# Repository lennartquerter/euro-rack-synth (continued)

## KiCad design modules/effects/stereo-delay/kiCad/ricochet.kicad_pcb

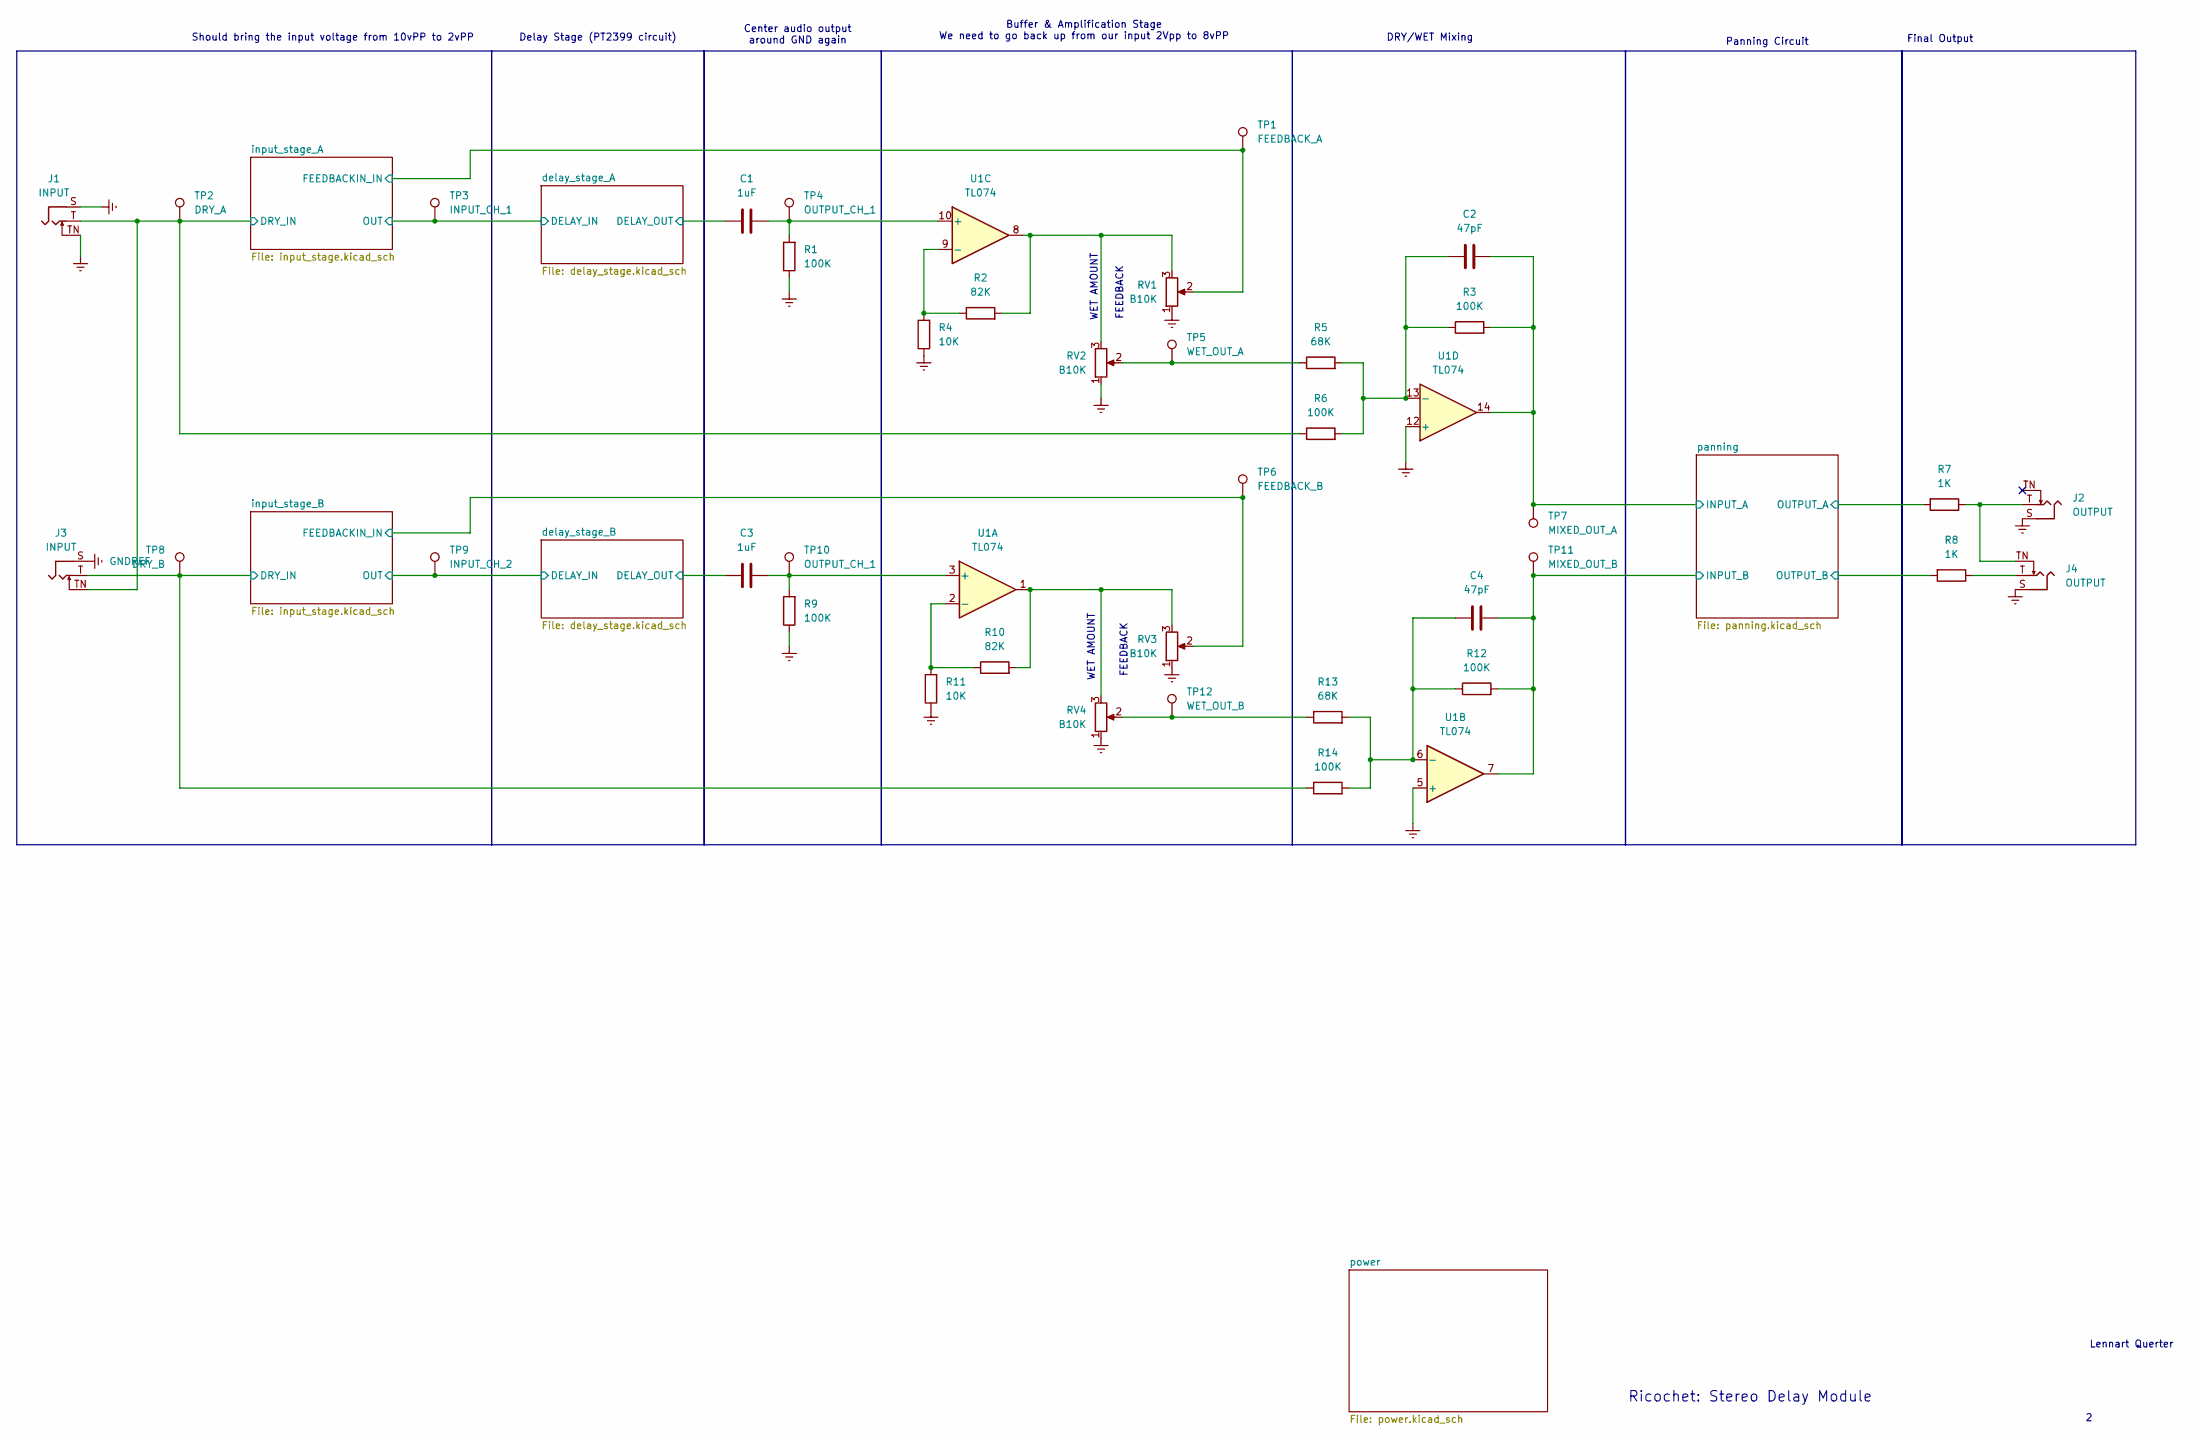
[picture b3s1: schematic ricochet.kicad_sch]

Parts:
C1, C3: 1uF; C_0805_2012Metric_Pad1.18x1.45mm_HandSolder
C2, C4: 47pF; C_0805_2012Metric_Pad1.18x1.45mm_HandSolder
J1, J3: INPUT; Jack_3.5mm_QingPu_WQP-PJ398SM_Vertical_CircularHoles
J2, J4: OUTPUT; Jack_3.5mm_QingPu_WQP-PJ398SM_Vertical_CircularHoles
R1, R3, R6, R9, R12, R14: 100K; R_0805_2012Metric_Pad1.20x1.40mm_HandSolder
R2, R10: 82K; R_0805_2012Metric_Pad1.20x1.40mm_HandSolder
R4, R11: 10K; R_0805_2012Metric_Pad1.20x1.40mm_HandSolder
R5, R13: 68K; R_0805_2012Metric_Pad1.20x1.40mm_HandSolder
R7, R8: 1K; R_0805_2012Metric_Pad1.20x1.40mm_HandSolder
RV1, RV2, RV3, RV4: B10K; Potentiometer_TT_P0915N
TP1: FEEDBACK_A; Pin_D1.0mm_L10.0mm
TP2: DRY_A; Pin_D1.0mm_L10.0mm
TP3: INPUT_CH_1; Pin_D1.0mm_L10.0mm
TP4, TP10: OUTPUT_CH_1; Pin_D1.0mm_L10.0mm
TP5: WET_OUT_A; Pin_D1.0mm_L10.0mm
TP6: FEEDBACK_B; Pin_D1.0mm_L10.0mm
TP7: MIXED_OUT_A; Pin_D1.0mm_L10.0mm
TP8: DRY_B; Pin_D1.0mm_L10.0mm
TP9: INPUT_CH_2; Pin_D1.0mm_L10.0mm
TP11: MIXED_OUT_B; Pin_D1.0mm_L10.0mm
TP12: WET_OUT_B; Pin_D1.0mm_L10.0mm
U1: TL074; SOIC-14

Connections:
/delay_stage_A/DELAY_IN: TP3.1; also elsewhere on the board
/delay_stage_A/DELAY_OUT: C1.1; also elsewhere on the board
/delay_stage_B/DELAY_IN: TP9.1; also elsewhere on the board
/delay_stage_B/DELAY_OUT: C3.1; also elsewhere on the board
/input_stage_A/DRY_IN: J1.T, J3.TN, R6.1, TP2.1; also elsewhere on the board
/input_stage_A/FEEDBACKIN_IN: RV1.2, TP1.1; also elsewhere on the board
/input_stage_B/DRY_IN: J3.T, R14.1, TP8.1; also elsewhere on the board
/input_stage_B/FEEDBACKIN_IN: RV3.2, TP6.1; also elsewhere on the board
/panning/INPUT_A: C2.2, R3.2, TP7.1, U1.14; also elsewhere on the board
/panning/INPUT_B: C4.2, R12.2, TP11.1, U1.7; also elsewhere on the board
/panning/OUTPUT_A: R7.2; also elsewhere on the board
/panning/OUTPUT_B: R8.2; also elsewhere on the board
GNDREF: J1.S, J1.TN, J2.S, J3.S, J4.S, R1.1, R4.1, R9.1, R11.1, RV1.1, RV2.1, RV3.1, RV4.1, U1.5 (+), U1.12 (+); also elsewhere on the board
unnamed: J2.T, J4.TN, R7.1
unnamed: J4.T, R8.1
unnamed: R2.2, RV1.3, RV2.3, U1.8
unnamed: R5.1, RV2.2, TP5.1
unnamed: R10.2, RV3.3, RV4.3, U1.1
unnamed: R13.1, RV4.2, TP12.1
unnamed: C3.2, R9.2, TP10.1, U1.3 (+)
unnamed: R10.1, R11.2, U1.2 (-)
unnamed: C4.1, R12.1, R13.2, R14.2, U1.6 (-)
unnamed: C1.2, R1.2, TP4.1, U1.10 (+)
unnamed: R2.1, R4.2, U1.9 (-)
unnamed: C2.1, R3.1, R5.2, R6.2, U1.13 (-)

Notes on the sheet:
Should bring the input voltage from 10vPP to 2vPP
FEEDBACK
DRY/WET Mixing
Panning Circuit
WET AMOUNT
Delay Stage (PT2399 circuit)
Center audio output around GND again
Lennart Querter
Final Output
Ricochet: Stereo Delay Module
Buffer & Amplification Stage We need to go back up from our input 2Vpp to 8vPP

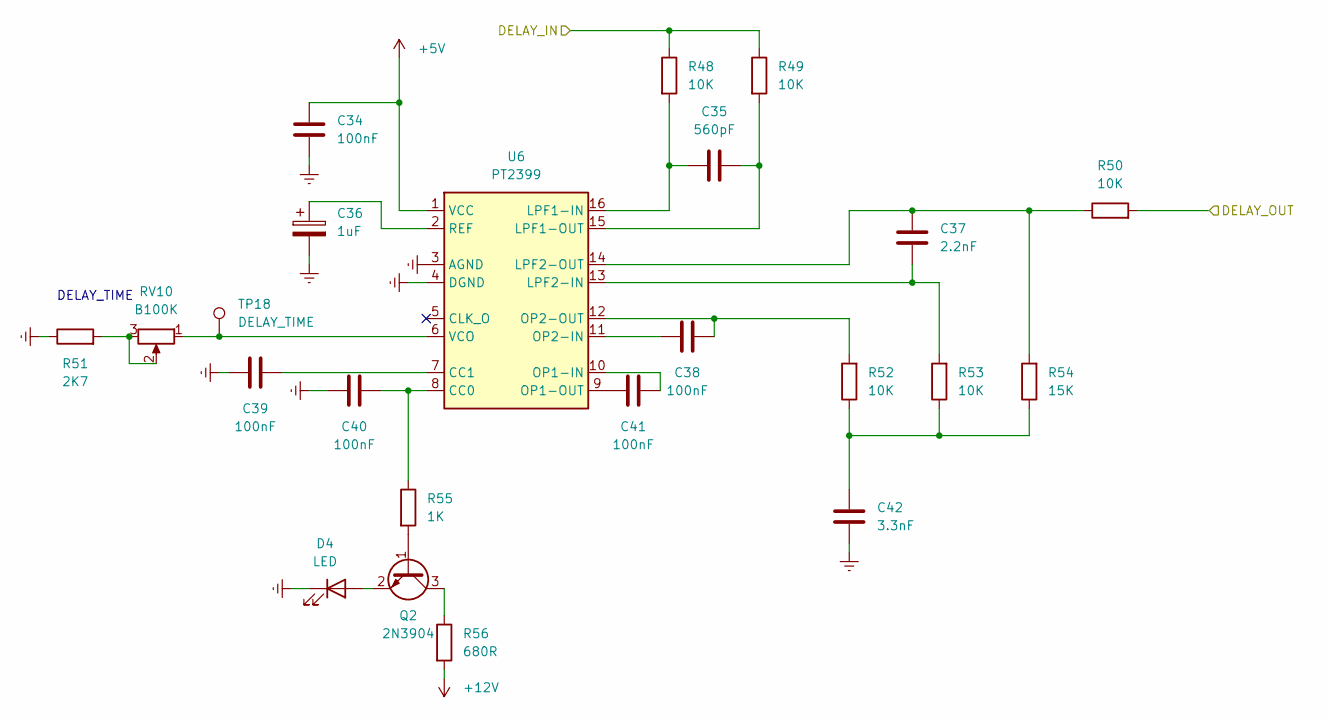
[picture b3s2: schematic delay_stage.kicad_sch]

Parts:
C34, C38, C39, C40, C41: 100nF; C_0805_2012Metric_Pad1.18x1.45mm_HandSolder
C35: 560pF; C_0805_2012Metric_Pad1.18x1.45mm_HandSolder
C36: 1uF; CP_Radial_D4.0mm_P2.00mm
C37: 2.2nF; C_0805_2012Metric_Pad1.18x1.45mm_HandSolder
C42: 3.3nF; C_0805_2012Metric_Pad1.18x1.45mm_HandSolder
D4: LED; LED_D3.0mm
Q2: 2N3904; SOT-23
R48, R49, R50, R52, R53: 10K; R_0805_2012Metric_Pad1.20x1.40mm_HandSolder
R51: 2K7; R_0805_2012Metric_Pad1.20x1.40mm_HandSolder
R54: 15K; R_0805_2012Metric_Pad1.20x1.40mm_HandSolder
R55: 1K; R_0805_2012Metric_Pad1.20x1.40mm_HandSolder
R56: 680R; R_0805_2012Metric_Pad1.20x1.40mm_HandSolder
RV10: B100K; Potentiometer_TT_P0915N
TP18: DELAY_TIME; Pin_D1.0mm_L10.0mm
U6: PT2399; SOIC-16

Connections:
+5V: C34.2, U6.1 (VCC); also elsewhere on the board
+12V: R56.2; also elsewhere on the board
/delay_stage_B/DELAY_IN: R48.1, R49.1; also elsewhere on the board
/delay_stage_B/DELAY_OUT: R50.2; also elsewhere on the board
GNDREF: C34.1, C36.2, C39.1, C40.2, C42.2, D4.1 (K), R51.1, U6.3 (AGND), U6.4 (DGND); also elsewhere on the board
unnamed: C42.1, R52.1, R53.1, R54.1
unnamed: D4.2 (A), Q2.2 (E)
unnamed: Q2.1 (B), R55.2
unnamed: Q2.3 (C), R56.1
unnamed: R51.2, RV10.2, RV10.3
unnamed: C40.1, R55.1, U6.8 (CC0)
unnamed: C39.2, U6.7 (CC1)
unnamed: C35.1, R48.2, U6.16 (LPF1-IN)
unnamed: C35.2, R49.2, U6.15 (LPF1-OUT)
unnamed: C37.2, R53.2, U6.13 (LPF2-IN)
unnamed: C37.1, R50.1, R54.2, U6.14 (LPF2-OUT)
unnamed: C41.1, U6.10 (OP1-IN)
unnamed: C41.2, U6.9 (OP1-OUT)
unnamed: C38.2, U6.11 (OP2-IN)
unnamed: C38.1, R52.2, U6.12 (OP2-OUT)
unnamed: C36.1, U6.2 (REF)
unnamed: RV10.1, TP18.1, U6.6 (VCO)

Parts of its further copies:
C20, C24, C25, C26, C27: 100nF; C_0805_2012Metric_Pad1.18x1.45mm_HandSolder
C21: 560pF; C_0805_2012Metric_Pad1.18x1.45mm_HandSolder
C22: 1uF; CP_Radial_D4.0mm_P2.00mm
C23: 2.2nF; C_0805_2012Metric_Pad1.18x1.45mm_HandSolder
C28: 3.3nF; C_0805_2012Metric_Pad1.18x1.45mm_HandSolder
D3: LED; LED_D3.0mm
Q1: 2N3904; SOT-23
R22, R23, R24, R26, R27: 10K; R_0805_2012Metric_Pad1.20x1.40mm_HandSolder
R25: 2K7; R_0805_2012Metric_Pad1.20x1.40mm_HandSolder
R28: 15K; R_0805_2012Metric_Pad1.20x1.40mm_HandSolder
R29: 1K; R_0805_2012Metric_Pad1.20x1.40mm_HandSolder
R30: 680R; R_0805_2012Metric_Pad1.20x1.40mm_HandSolder
RV6: B100K; Potentiometer_TT_P0915N
TP17: DELAY_TIME; Pin_D1.0mm_L10.0mm
U5: PT2399; SOIC-16

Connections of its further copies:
+5V: C20.2, U5.1 (VCC); also elsewhere on the board
+12V: R30.2; also elsewhere on the board
/delay_stage_A/DELAY_IN: R22.1, R23.1; also elsewhere on the board
/delay_stage_A/DELAY_OUT: R24.2; also elsewhere on the board
GNDREF: C20.1, C22.2, C25.1, C26.2, C28.2, D3.1 (K), R25.1, U5.3 (AGND), U5.4 (DGND); also elsewhere on the board
unnamed: C28.1, R26.1, R27.1, R28.1
unnamed: D3.2 (A), Q1.2 (E)
unnamed: Q1.1 (B), R29.2
unnamed: Q1.3 (C), R30.1
unnamed: R25.2, RV6.2, RV6.3
unnamed: C26.1, R29.1, U5.8 (CC0)
unnamed: C25.2, U5.7 (CC1)
unnamed: C21.1, R22.2, U5.16 (LPF1-IN)
unnamed: C21.2, R23.2, U5.15 (LPF1-OUT)
unnamed: C23.2, R27.2, U5.13 (LPF2-IN)
unnamed: C23.1, R24.1, R28.2, U5.14 (LPF2-OUT)
unnamed: C27.1, U5.10 (OP1-IN)
unnamed: C27.2, U5.9 (OP1-OUT)
unnamed: C24.2, U5.11 (OP2-IN)
unnamed: C24.1, R26.2, U5.12 (OP2-OUT)
unnamed: C22.1, U5.2 (REF)
unnamed: RV6.1, TP17.1, U5.6 (VCO)

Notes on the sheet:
DELAY_TIME

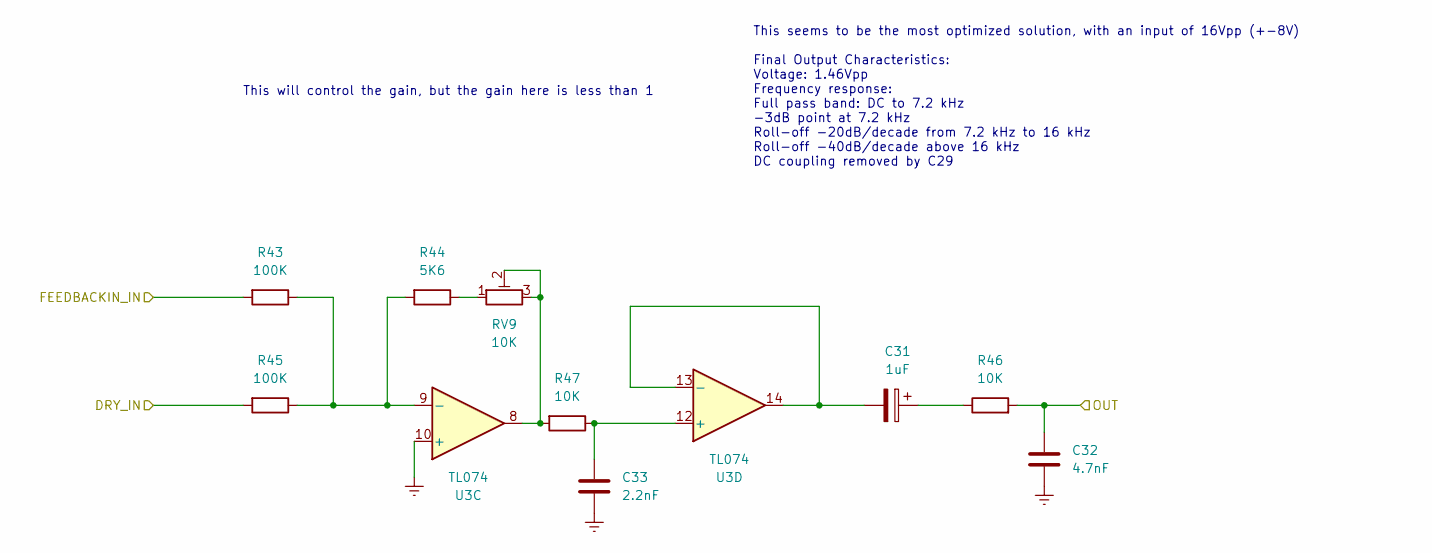
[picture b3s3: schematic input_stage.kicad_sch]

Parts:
C31: 1uF; CP_Radial_D4.0mm_P2.00mm
C32: 4.7nF; C_0805_2012Metric_Pad1.18x1.45mm_HandSolder
C33: 2.2nF; C_0805_2012Metric_Pad1.18x1.45mm_HandSolder
R43, R45: 100K; R_0805_2012Metric_Pad1.20x1.40mm_HandSolder
R44: 5K6; R_0805_2012Metric_Pad1.20x1.40mm_HandSolder
R46, R47: 10K; R_0805_2012Metric_Pad1.20x1.40mm_HandSolder
RV9: 10K; Potentiometer_ACP_CA6-VSMD_Vertical
U3: TL074; SOIC-14

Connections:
/delay_stage_A/DELAY_IN: C32.2, R46.2; also elsewhere on the board
/input_stage_A/DRY_IN: R45.2; also elsewhere on the board
/input_stage_A/FEEDBACKIN_IN: R43.2; also elsewhere on the board
GNDREF: C32.1, C33.1, U3.3 (+), U3.10 (+); also elsewhere on the board
unnamed: C31.1, R46.1
unnamed 37: U3.1; also elsewhere on the board
unnamed: R44.1, RV9.1
unnamed: R47.2, RV9.2, RV9.3, U3.8
unnamed 54: U3.2 (-); also elsewhere on the board
unnamed 55: U3.5 (+); also elsewhere on the board
unnamed 56: U3.6 (-), U3.7; also elsewhere on the board
unnamed: R43.1, R44.2, R45.1, U3.9 (-)
unnamed: C33.2, R47.1, U3.12 (+)
unnamed: C31.2, U3.13 (-), U3.14

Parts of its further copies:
C17: 1uF; CP_Radial_D4.0mm_P2.00mm
C18: 4.7nF; C_0805_2012Metric_Pad1.18x1.45mm_HandSolder
C19: 2.2nF; C_0805_2012Metric_Pad1.18x1.45mm_HandSolder
R17, R19: 100K; R_0805_2012Metric_Pad1.20x1.40mm_HandSolder
R18: 5K6; R_0805_2012Metric_Pad1.20x1.40mm_HandSolder
R20, R21: 10K; R_0805_2012Metric_Pad1.20x1.40mm_HandSolder
RV5: 10K; Potentiometer_ACP_CA6-VSMD_Vertical

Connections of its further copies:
/delay_stage_B/DELAY_IN: C18.2, R20.2; also elsewhere on the board
/input_stage_B/DRY_IN: R19.2; also elsewhere on the board
/input_stage_B/FEEDBACKIN_IN: R17.2; also elsewhere on the board
GNDREF: C18.1, C19.1; also elsewhere on the board
unnamed: C17.1, R20.1
unnamed: R18.1, RV5.1
unnamed 37: R21.2, RV5.2, RV5.3; also elsewhere on the board
unnamed 54: R17.1, R18.2, R19.1; also elsewhere on the board
unnamed 55: C19.2, R21.1; also elsewhere on the board
unnamed 56: C17.2; also elsewhere on the board

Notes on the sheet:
This seems to be the most optimized solution, with an input of 16Vpp (+-8V) Final Output Characteristics: Voltage: 1.46Vpp Frequency response: Full pass band: DC to 7.2 kHz -3dB point at 7.2 kHz Roll-off -20dB/decade from 7.2 kHz to 16 kHz Roll-off -40dB/decade above 16 kHz DC coupling removed by C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
This will control the gain, but the gain here is less than 1

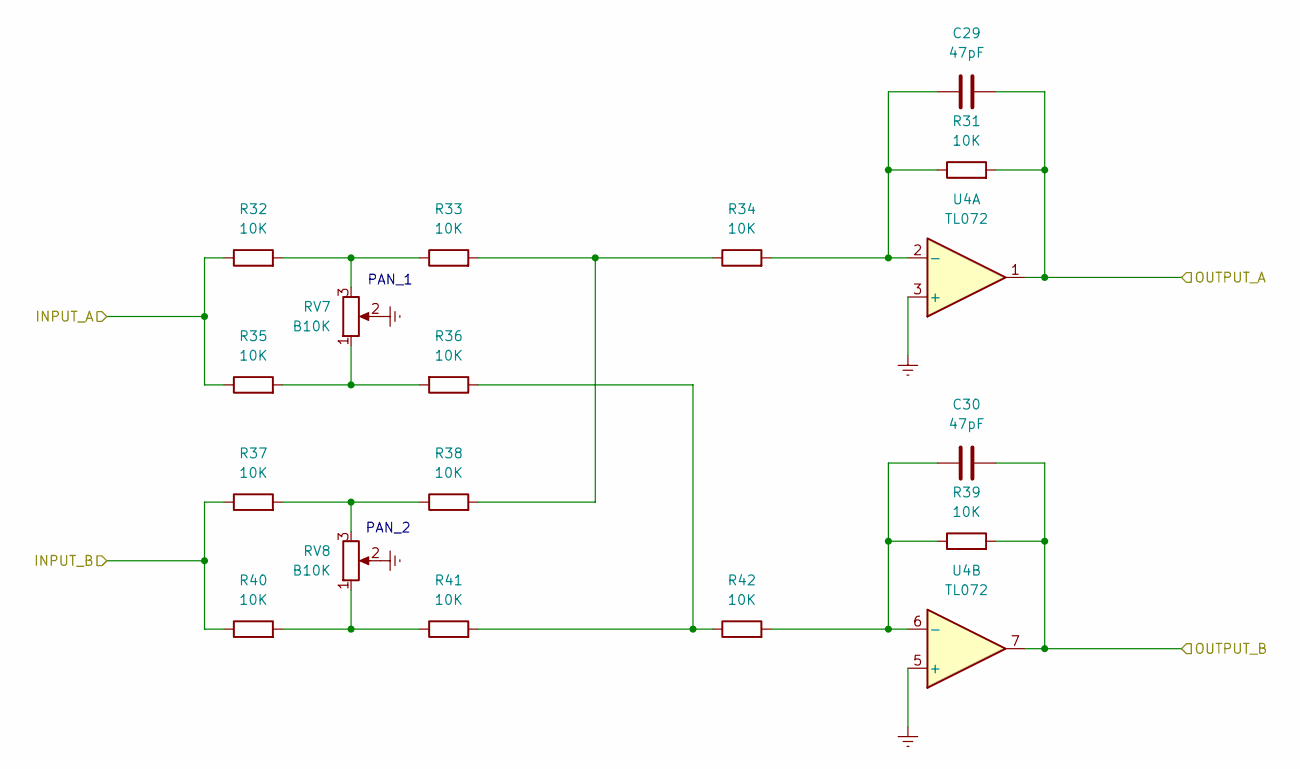
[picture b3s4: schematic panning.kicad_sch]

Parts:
C29, C30: 47pF; C_0805_2012Metric_Pad1.18x1.45mm_HandSolder
R31, R32, R33, R34, R35, R36, R37, R38, R39, R40, R41, R42: 10K; R_0805_2012Metric_Pad1.20x1.40mm_HandSolder
RV7, RV8: B10K; Potentiometer_TT_P0915N
U4: TL072; SOIC-8

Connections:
/panning/INPUT_A: R32.1, R35.1; also elsewhere on the board
/panning/INPUT_B: R37.1, R40.1; also elsewhere on the board
/panning/OUTPUT_A: C29.2, R31.2, U4.1; also elsewhere on the board
/panning/OUTPUT_B: C30.2, R39.2, U4.7; also elsewhere on the board
GNDREF: RV7.2, RV8.2, U4.3 (+), U4.5 (+); also elsewhere on the board
unnamed: R32.2, R33.1, RV7.3
unnamed: R33.2, R34.1, R38.2
unnamed: R35.2, R36.2, RV7.1
unnamed: R36.1, R41.2, R42.1
unnamed: R37.2, R38.1, RV8.3
unnamed: R40.2, R41.1, RV8.1
unnamed: C29.1, R31.1, R34.2, U4.2 (-)
unnamed: C30.1, R39.1, R42.2, U4.6 (-)

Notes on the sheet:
PAN_2
PAN_1

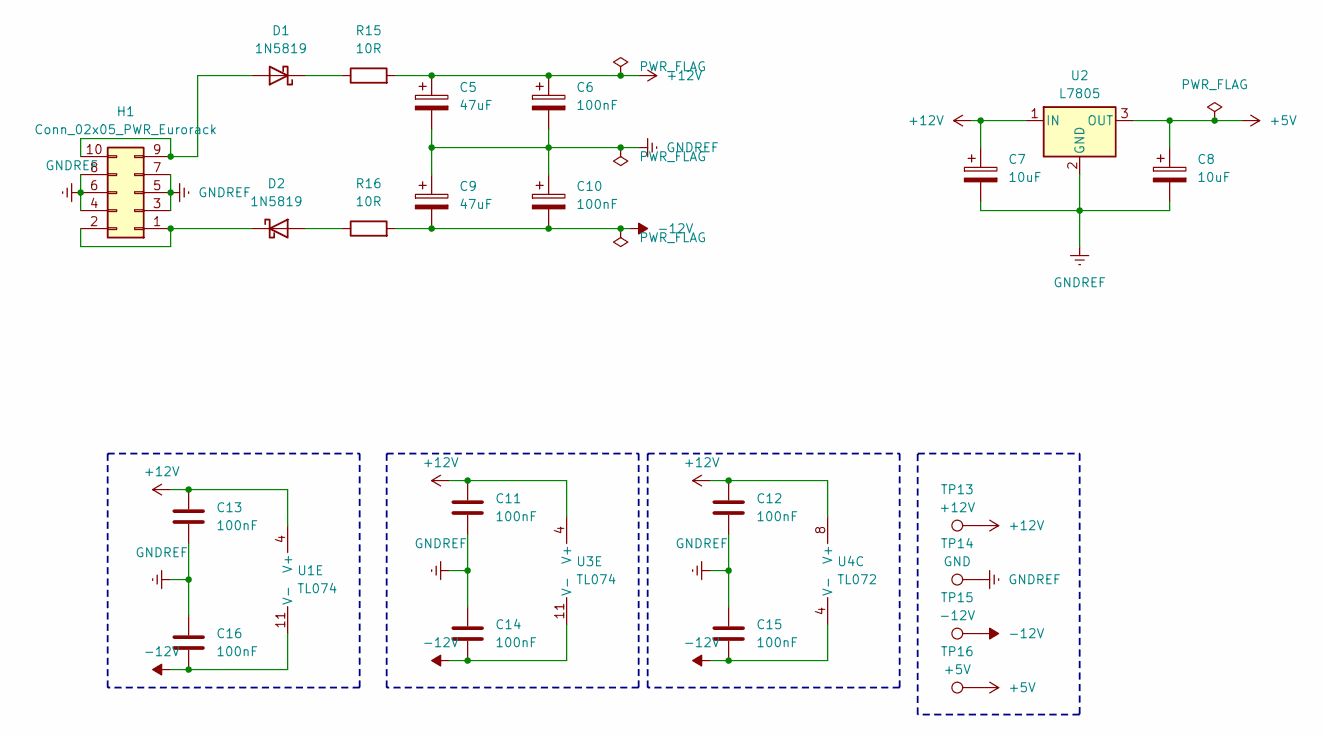
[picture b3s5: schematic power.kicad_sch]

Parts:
C5, C9: 47uF; CP_Radial_D6.3mm_P2.50mm
C6, C10: 100nF; CP_Radial_D4.0mm_P2.00mm
C7, C8: 10uF; CP_Radial_D4.0mm_P2.00mm
C11, C12, C13, C14, C15, C16: 100nF; C_0805_2012Metric_Pad1.18x1.45mm_HandSolder
D1, D2: 1N5819; D_SOD-123
H1: Conn_02x05_PWR_Eurorack; IDC-Header_2x05_P2.54mm_Vertical
R15, R16: 10R; R_0805_2012Metric_Pad1.20x1.40mm_HandSolder
TP13: +12V; Pin_D1.0mm_L10.0mm
TP14: GND; Pin_D1.0mm_L10.0mm
TP15: -12V; Pin_D1.0mm_L10.0mm
TP16: +5V; Pin_D1.0mm_L10.0mm
U1, U3: TL074; SOIC-14
U2: L7805; TO-252-2
U4: TL072; SOIC-8

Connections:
+5V: C8.1, TP16.1, U2.3 (OUT); also elsewhere on the board
+12V: C5.1, C6.1, C7.1, C11.1, C12.1, C13.1, R15.2, TP13.1, U1.4 (V+), U2.1 (IN), U3.4 (V+), U4.8 (V+); also elsewhere on the board
-12V: C9.2, C10.2, C14.2, C15.2, C16.2, R16.2, TP15.1, U1.11 (V-), U3.11 (V-), U4.4 (V-)
GNDREF: C5.2, C6.2, C7.2, C8.2, C9.1, C10.1, C11.2, C12.2, C13.2, C14.1, C15.1, C16.1, H1.3, H1.4, H1.5, H1.6, H1.7, H1.8, TP14.1, U2.2 (GND), U3.3 (+); also elsewhere on the board
unnamed: D1.2 (A), H1.9, H1.10
unnamed: D1.1 (K), R15.1
unnamed: D2.2 (A), R16.1
unnamed: D2.1 (K), H1.1, H1.2
unnamed 37: U3.1; also elsewhere on the board
unnamed 54: U3.2 (-); also elsewhere on the board
unnamed 55: U3.5 (+); also elsewhere on the board
unnamed 56: U3.6 (-), U3.7; also elsewhere on the board

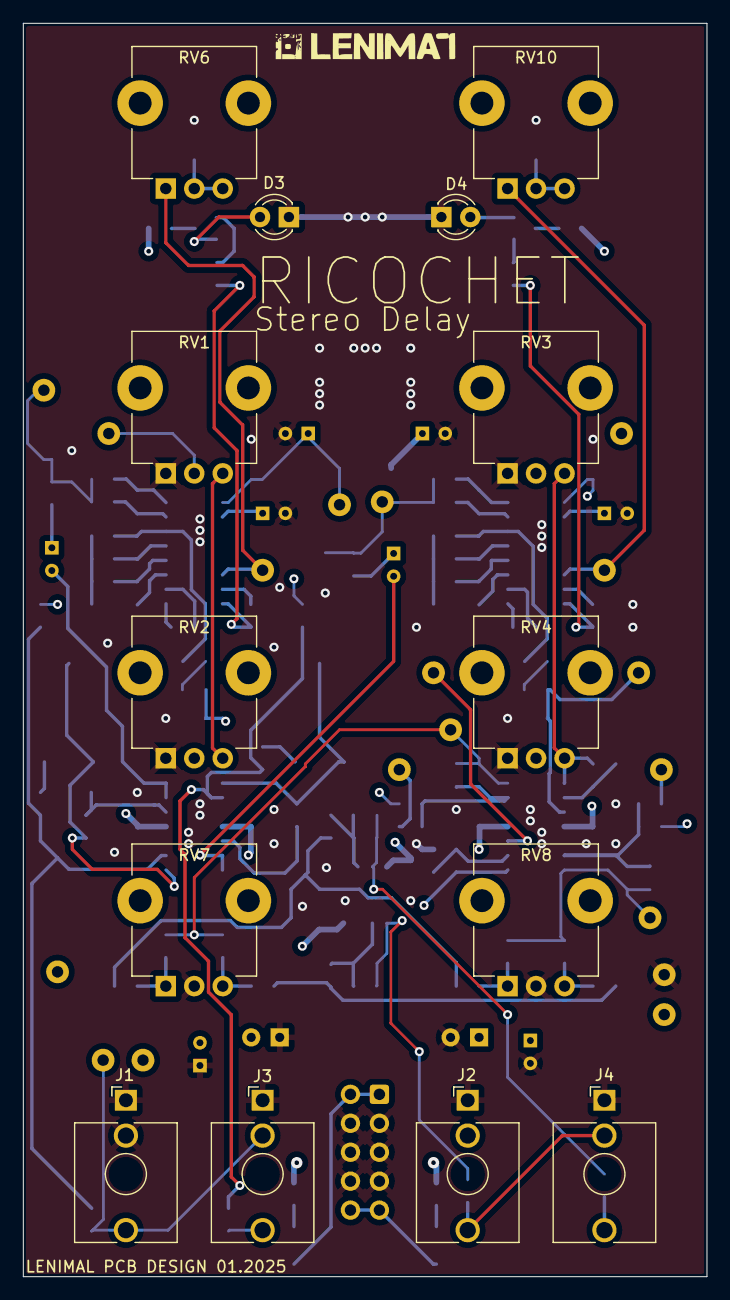
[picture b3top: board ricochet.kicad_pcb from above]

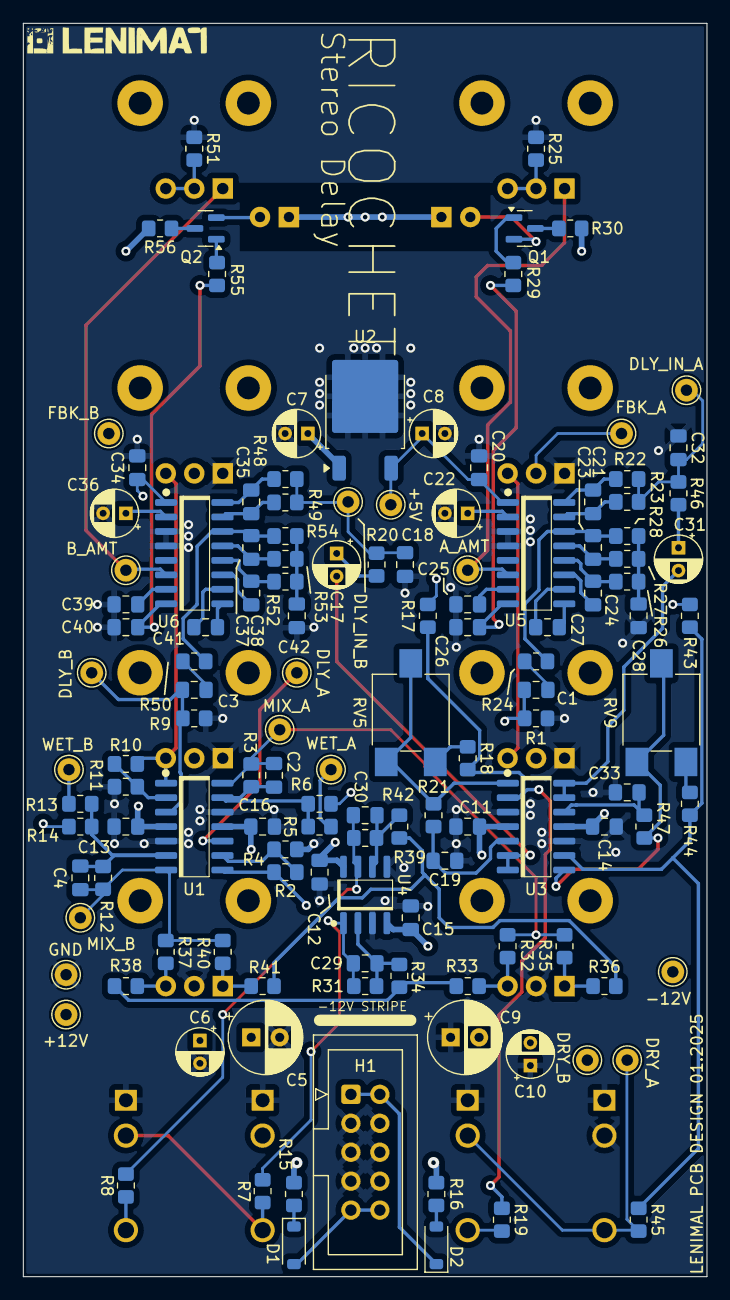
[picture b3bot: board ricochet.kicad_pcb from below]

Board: 4 copper layers, 60.0 x 110.0 mm, 143 parts (129 on the bottom side), 86 nets.
